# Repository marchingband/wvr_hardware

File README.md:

# wvr_hardware

Find the Kicad files in their respective folders, more will be added with time.  
We have done our best to make these files portable, using project specific libraries.  
These are for Kicad V5.

In the JLC_PCB folder you can find all the files needed to order WVR BASIC from JLC with assembly. Kindly donated by Robin of Atonal Circuits.

There are 3 branches. v2.1 is the newest one, which includes a footprint for the XIAO SAMD21 on the back side, and a resistor on the front side to connect the UARTS.
click "main" above, and select v2.1 to move to this new branch
  
# pinouts

<pre>
pinout for WVR :

WVR PIN | MAKERS BOARD PIN | ESP32 GPIO | NOTES  
  
D0      |       14         |    3       | FTDI RX  
D1      |       13         |    1       | FTDI TX  
D2      |       12         |    21      | USB MIDI In (when using USB backpack firmware)  
D3      |       11         |    19      |  
D4      |       10         |    18      |  
D5      |       9          |    5       |  
D6      |       8          |    0       | no ADC when WIFI active, strapping pin for bootloader mode (must be high or floating at boot)  
D7      |       7          |    36      | no built-in pullups, input only  
D8      |       6          |    39      | no built-in pullups, input only  
D9      |       5          |    34      | no built-in pullups, input only  
D10     |       4          |    35      | no built-in pullups, input only  
D11     |       3          |    32      |  
D12     |       2          |    33      |  
D13     |       1          |    27      | no ADC when WIFI active  
</pre>  
  
# wiring diagram
Example of powering with the 5v pin, instead of the USB jack, with breadboard-compatible push button and headphone jack attached.  
When WVR's WiFi is active, current consumption can peak significantly, as the radio consumes a fair bit of current. We recommend a PSU that provides 500mA or more at 5v. Any voltage between 5vDC and 9vDC will work, but keep in mind that higher voltage will result in more heat produced by the voltage regulator, which can get very hot! If you experience brown-outs during the boot sequence, try a PSU with a higher current rating.  

# wiring diagram for midi control
Example of controlling WVR from a RPi Pico using MIDI. Note that because MIDI is optically isolated, both boards can be powered independantly, by USB, or otherwise. Thus there are no power rails connected in this diagram. It is also OK to power both boards from the same power source, it is just not necissary to do so.  
Note also, the MIDI signal does not use a ground connection. MIDI is a 2-line protocol, just +5v and TX are needed.  
Here is a great Arduino library to generate MIDI signals from the RPi Pico, or most any other microcontroller: https://github.com/FortySevenEffects/arduino_midi_library

This code snippet for the PiPico sends some basic MIDI messages and flashes the onboard LED.
```
#include <Arduino.h>
#include <MIDI.h>

using Transport = MIDI_NAMESPACE::SerialMIDI<HardwareSerial>;
Transport serialMIDI(Serial1);
MIDI_NAMESPACE::MidiInterface<Transport> MIDI((Transport&)serialMIDI);

void setup()
{
  pinMode(LED_BUILTIN, OUTPUT);
  MIDI.begin(MIDI_CHANNEL_OMNI); // Launch MIDI
}

void loop()
{
    MIDI.sendNoteOn(40, 127, 1);    // Send a Note (pitch 40, velocity 127 on channel 1)
    digitalWrite(LED_BUILTIN, HIGH);
    delay(1000);                    // Wait for a second
    MIDI.sendNoteOff(40, 0, 1);     // Stop the note
    digitalWrite(LED_BUILTIN, LOW);
    delay(1000);
}
```

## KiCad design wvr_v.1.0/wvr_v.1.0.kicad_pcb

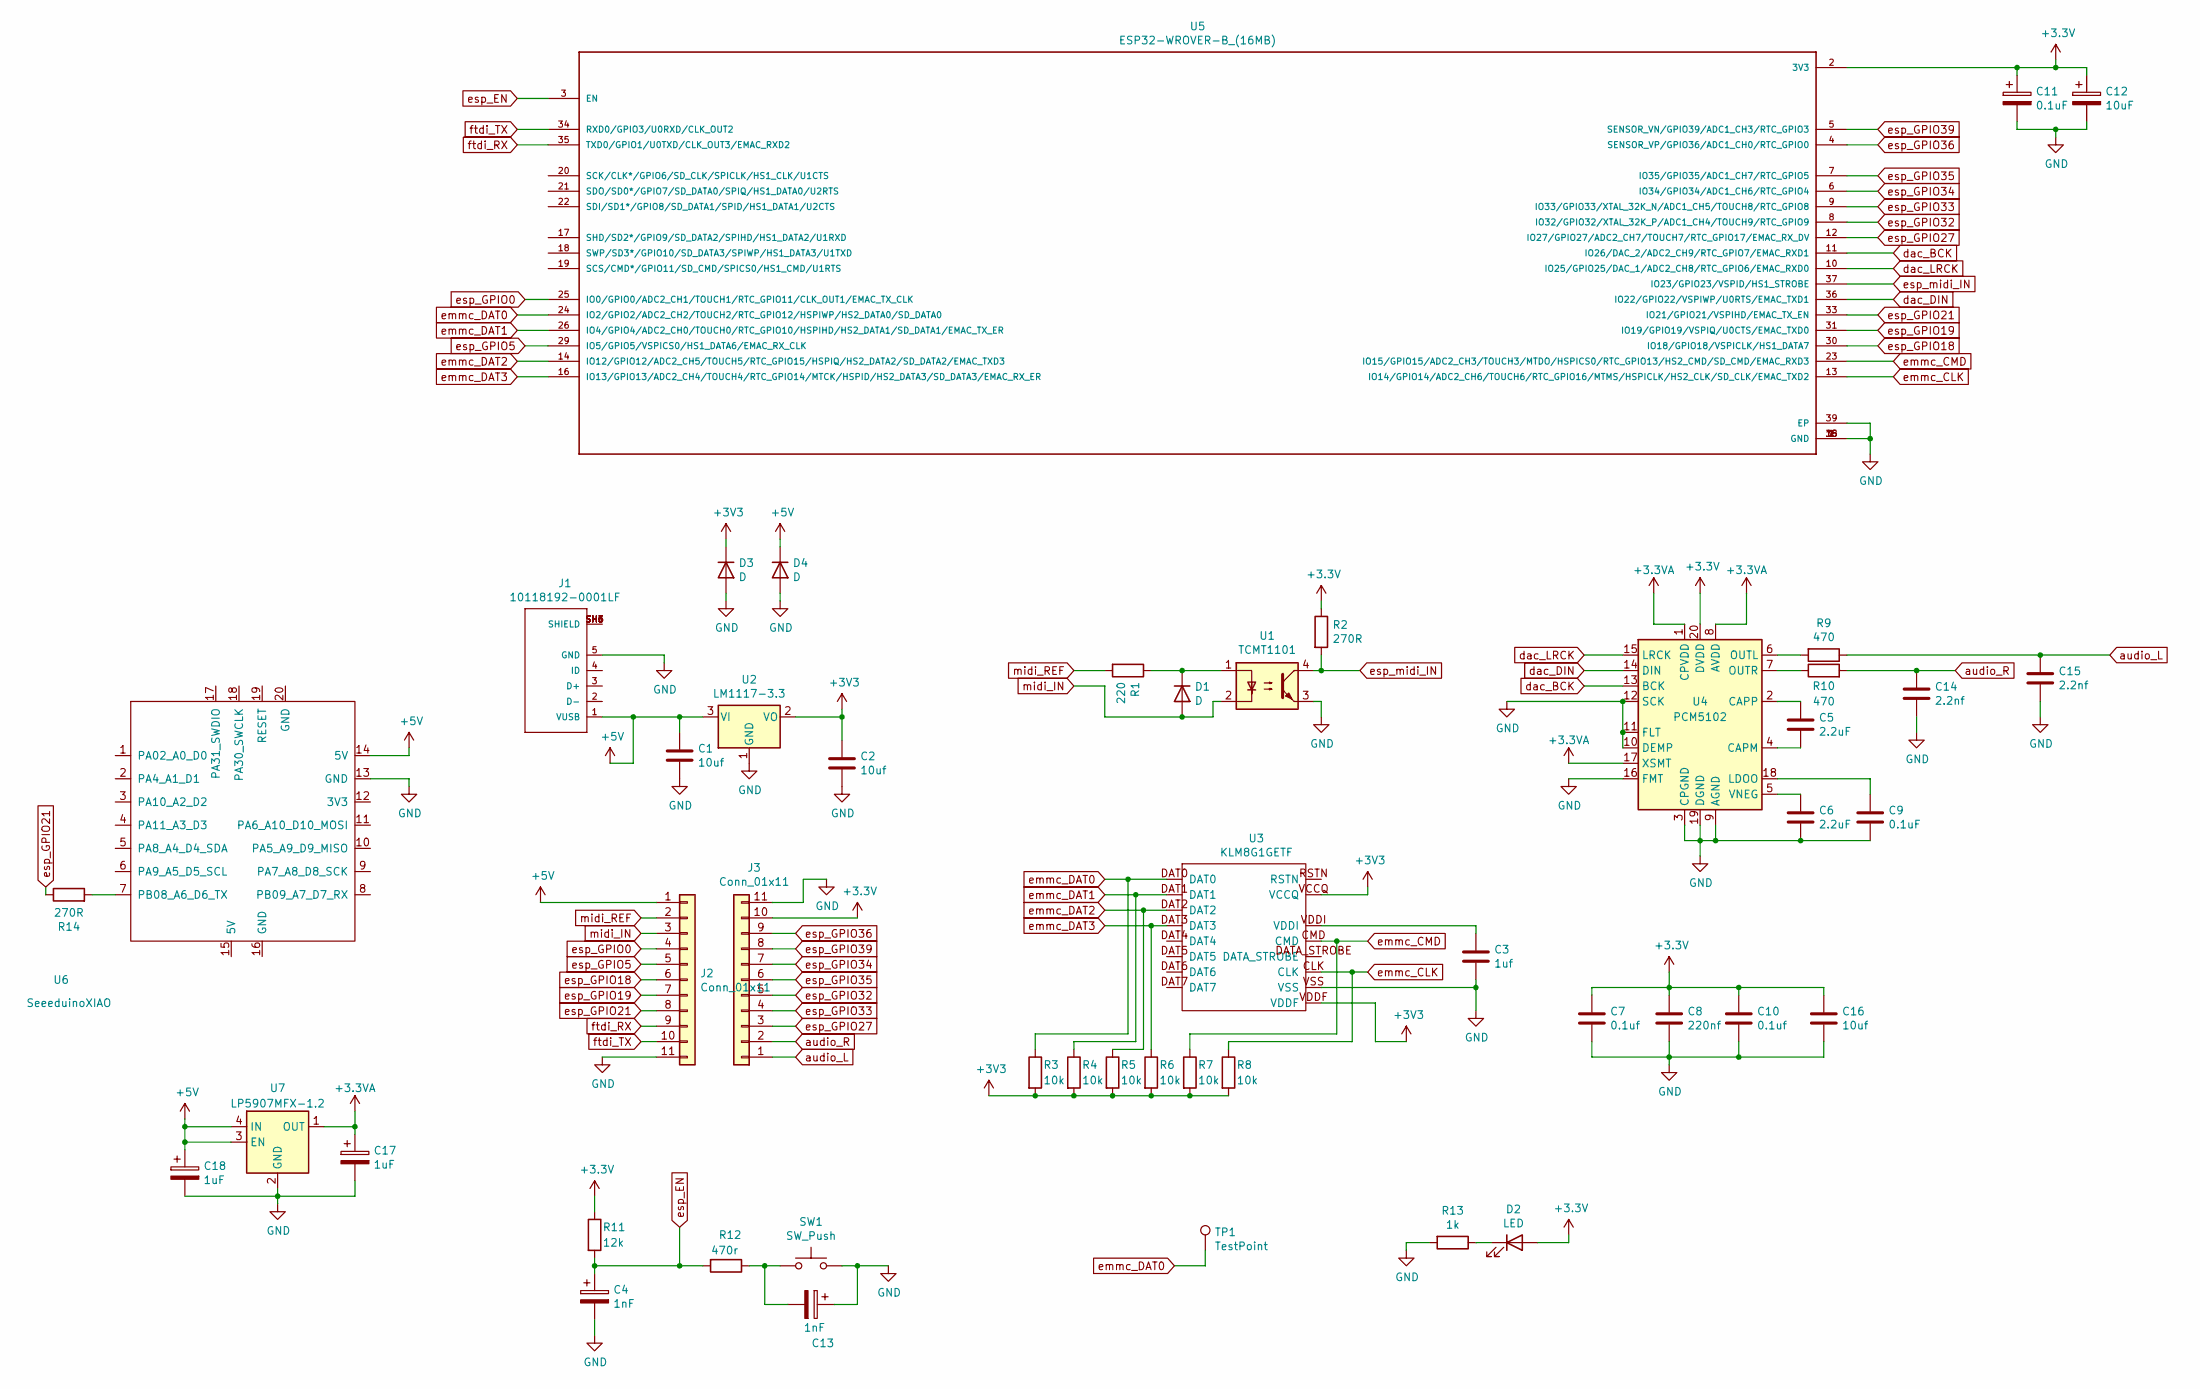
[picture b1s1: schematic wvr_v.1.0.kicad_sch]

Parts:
C1, C2, C16: 10uf; C_0402_1005Metric
C3: 1uf; C_0402_1005Metric
C4, C13: 1nF; C_0402_1005Metric
C5, C6: 2.2uF; C_0402_1005Metric
C7, C10: 0.1uf; C_0402_1005Metric
C8: 220nf; C_0402_1005Metric
C9, C11: 0.1uF; C_0402_1005Metric
C12: 10uF; C_0402_1005Metric
C14, C15: 2.2nf; C_0402_1005Metric
C17, C18: 1uF; C_0402_1005Metric
D1, D3, D4: D; D_SOD-323
D2: LED; LED_0603_1608Metric
J1: 10118192-0001LF; USB-MICRO-B_C40942
J2: Conn_01x11; CAST_HEADER_11_LEFT_2
J3: Conn_01x11; CAST_HEADER_11_RIGHT_2
R1: 220; R_0402_1005Metric
R2, R14: 270R; R_0402_1005Metric
R3, R4, R5, R6, R7, R8: 10k; R_0402_1005Metric
R9, R10: 470; R_0402_1005Metric
R11: 12k; R_0402_1005Metric
R12: 470r; R_0402_1005Metric
R13: 1k; R_0402_1005Metric
SW1: SW_Push; SW_Push_SPST_NO_Alps_SKRK
TP1: TestPoint; TestPoint_Pad_D1.5mm
U1: TCMT1101; SOP-4_4.4x2.6mm_P1.27mm
U2: LM1117-3.3; SOT-223-3_TabPin2; LCSC C23984
U3: KLM8G1GETF; KLM8G1GETF_ALL_PADS; LCSC C499918
U4: PCM5102; TSSOP-20_4.4x6.5mm_P0.65mm; LCSC C131154
U5: ESP32-WROVER-B_(16MB); XCVR_ESP32-WROVER-B_(16MB); LCSC C529591
U6: SeeeduinoXIAO; Seeeduino XIAO-MOUDLE14P-2.54-21X17.8MM
U7: LP5907MFX-1.2; Texas_X2SON-4_1x1mm_P0.65mm

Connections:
+5V: C1.1, C18.1, D4.1 (K), J1.1 (VUSB), J2.1, U2.3 (VI), U6.14 (5V), U7.3 (EN), U7.4 (IN)
GND: C1.2, C2.2, C3.2, C4.2, C6.2, C7.2, C8.2, C9.2, C10.2, C11.2, C12.2, C13.1, C14.2, C15.2, C16.2, C17.2, C18.2, D3.2 (A), D4.2 (A), J1.5 (GND), J2.11, J3.11, R13.2, SW1.2, U1.3, U2.1 (GND), U3.VSS, U4.3 (CPGND), U4.9 (AGND), U4.10 (DEMP), U4.11 (FLT), U4.12 (SCK), U4.16 (FMT), U4.19 (DGND), U5.1 (GND), U5.15 (GND), U5.38 (GND), U5.39 (EP), U6.13 (GND), U7.2 (GND)
unnamed: C3.1, U3.VDDI
unnamed: C5.1, U4.2 (CAPP)
unnamed: C5.2, U4.4 (CAPM)
unnamed: C6.1, U4.5 (VNEG)
unnamed: C9.1, U4.18 (LDOO)
unnamed: C13.2, R12.1, SW1.1
unnamed: D1.1 (K), R1.1, U1.1
unnamed: D2.1 (K), R13.1
unnamed: J1.SH3 (SHIELD), J1.SH4 (SHIELD), J1.SH5 (SHIELD), J1.SH6 (SHIELD)
unnamed: R9.2, U4.6 (OUTL)
unnamed: R10.1, U4.7 (OUTR)
unnamed: R14.2, U6.7 (PB08_A6_D6_TX)
audio_L: C15.1, J3.1, R9.1
audio_R: C14.1, J3.2, R10.2
dac_BCK: U4.13 (BCK), U5.11 (IO26/DAC_2/ADC2_CH9/RTC_GPIO7/EMAC_RXD1)
dac_DIN: U4.14 (DIN), U5.36 (IO22/GPIO22/VSPIWP/U0RTS/EMAC_TXD1)
dac_LRCK: U4.15 (LRCK), U5.10 (IO25/GPIO25/DAC_1/ADC2_CH8/RTC_GPIO6/EM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)
emmc_CLK: R8.1, U3.CLK, U5.13 (IO14/GPIO14/ADC2_CH6/TOUCH6/RTC_GPIO16/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)
emmc_CMD: R7.1, U3.CMD, U5.23 (IO15/GPIO15/ADC2_CH3/TOUCH3/MTDO/HSPICS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)
emmc_DAT0: R3.1, TP1.1, U3.DAT0, U5.24 (IO2/GPIO2/ADC2_CH2/TOUCH2/RTC_GPIO12/HS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); also elsewhere on the board
emmc_DAT1: R4.1, U3.DAT1, U5.26 (IO4/GPIO4/ADC2_CH0/TOUCH0/RTC_GPIO10/HS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)
emmc_DAT2: R5.1, U3.DAT2, U5.14 (IO12/GPIO12/ADC2_CH5/TOUCH5/RTC_GPIO15/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)
emmc_DAT3: R6.1, U3.DAT3, U5.16 (IO13/GPIO13/ADC2_CH4/TOUCH4/RTC_GPIO14/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)
esp_EN: C4.1, R11.2, R12.2, U5.3 (EN)
esp_GPIO0: J2.4, U5.25 (IO0/GPIO0/ADC2_CH1/TOUCH1/RTC_GPIO11/CL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)
esp_GPIO5: J2.5, U5.29 (IO5/GPIO5/VSPICS0/HS1_DATA6/EMAC_RX_CLK)
esp_GPIO18: J2.6, U5.30 (IO18/GPIO18/VSPICLK/HS1_DATA7)
esp_GPIO19: J2.7, U5.31 (IO19/GPIO19/VSPIQ/U0CTS/EMAC_TXD0)
esp_GPIO21: J2.8, R14.1, U5.33 (IO21/GPIO21/VSPIHD/EMAC_TX_EN)
esp_GPIO27: J3.3, U5.12 (IO27/GPIO27/ADC2_CH7/TOUCH7/RTC_GPIO17/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)
esp_GPIO32: J3.5, U5.8 (IO32/GPIO32/XTAL_32K_P/ADC1_CH4/TOUCH9/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)
esp_GPIO33: J3.4, U5.9 (IO33/GPIO33/XTAL_32K_N/ADC1_CH5/TOUCH8/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)
esp_GPIO34: J3.7, U5.6 (IO34/GPIO34/ADC1_CH6/RTC_GPIO4)
esp_GPIO35: J3.6, U5.7 (IO35/GPIO35/ADC1_CH7/RTC_GPIO5)
esp_GPIO36: J3.9, U5.4 (SENSOR_VP/GPIO36/ADC1_CH0/RTC_GPIO0)
esp_GPIO39: J3.8, U5.5 (SENSOR_VN/GPIO39/ADC1_CH3/RTC_GPIO3)
esp_midi_IN: R2.2, U1.4, U5.37 (IO23/GPIO23/VSPID/HS1_STROBE)
ftdi_RX: J2.9, U5.35 (TXD0/GPIO1/U0TXD/CLK_OUT3/EMAC_RXD2)
ftdi_TX: J2.10, U5.34 (RXD0/GPIO3/U0RXD/CLK_OUT2)
midi_IN: D1.2 (A), J2.3, U1.2
midi_REF: J2.2, R1.2

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
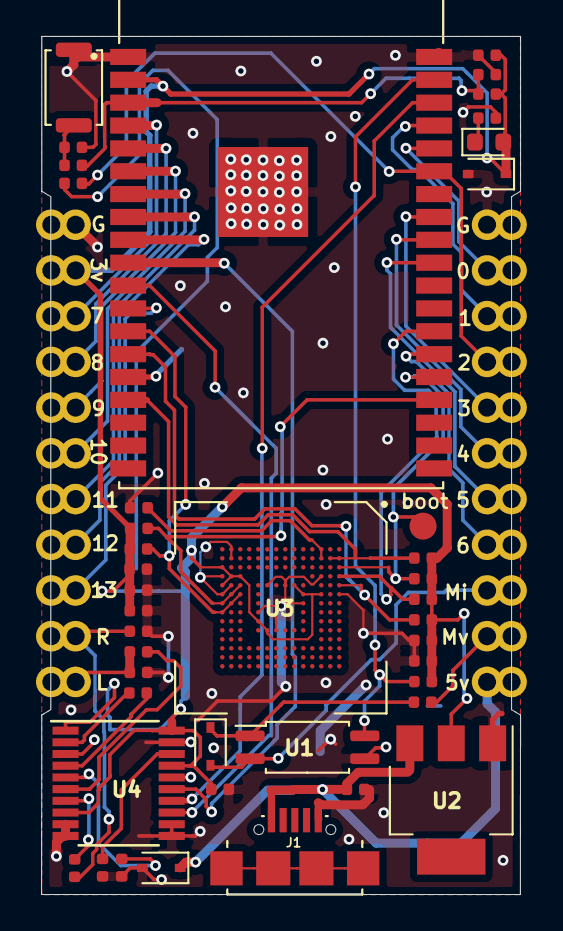
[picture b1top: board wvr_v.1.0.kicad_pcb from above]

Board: 2 copper layers, 26.6 x 47.7 mm, 45 parts (1 on the bottom side), 44 nets.

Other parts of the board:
boot: TestPoint; TestPoint_Pad_D1.5mm

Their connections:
emmc_DAT0: boot.1; also elsewhere on the board

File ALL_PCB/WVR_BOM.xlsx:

Item # | Designator | *Qty | Manufacturer | *Mfg Part # | Description / Value | *Package/Footprint | Type | Your Instructions / Notes
1 | C1,C2,C16 | 3 |  | C15525 | 10uf | 0402 | SMD
2 | C7,C10 | 2 |  | C1525 | 0.1uf | 0402 | SMD
3 | C12 | 1 |  | C15525 | 10uF | 0402 | SMD
4 | C14,C15 | 2 |  | C1531 | 2.2nf | 0402 | SMD
5 | C3 | 1 |  | C52923 | 1uf | 0402 | SMD
6 | C4,C13 | 2 |  | C1523 | 1nF | 0402 | SMD
7 | C5,C6 | 2 |  | C12530 | 2.2uF | 0402 | SMD
9 | C8 | 1 |  | C16772 | 220nf | 402 | SMD
10 | C9,C11 | 2 |  | C1525 | 0.1uF | 402 | SMD
11 | D1,D3,D4 | 3 |  | C2128 | D | SOD-323 | SMD
12 | D2 | 1 |  | C72041 | LED | 603 | SMD
13 | J1 | 1 |  | C40942 | usb b micro | 0402 | SMD
14 | R1 | 1 |  | C25091 | 220 | 0402 | SMD
15 | R11 | 1 |  | C25752 | 12k | 0402 | SMD
16 | R2 | 1 |  | C423200 | 280 | 402 | SDM
17 | R3,R4,R5,R6,R7,R8 | 6 |  | C25744 | 10k | 402 | SMD
18 | R9,R10,R12,R13,R14 | 4 |  | C25117 | 470 | 402 | SMD
19 | SW1 | 1 |  | C720477 | SW_Push | SKRK | SMD
20 | U1 | 1 |  | C32565 | EL3H7 | SOP-4 | SMD
21 | U2 | 1 |  | C6186 | LM1117-3.3 | SOT-223 SOT-223 | SMD
22 | U3 | 1 |  | C499918 | KLM8G1GETF | FBGA-153 | SMD
23 | U4 | 1 |  | C1540069 | PCM5100 | TSSOP-20 | SMD
24 | U5 | 1 |  | C503591 | ESP32-WROVER-B | XCVR_ESP32-WROVER-B | SMD

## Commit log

2021-08-06 readme
2021-08-06 shematic.png
2021-08-06 update schematic resistor values
2022-03-15 add JLC
2022-05-18 add images
2022-07-24 switch
2022-09-26 add usb midi resistor to front
2022-09-26 update silk layer, clean up .cpl file, print gerbers
2022-09-26 remove headers
2022-10-21 add dev board schematic pdf
2023-04-13 add wiring diagram
2023-04-30 update pinout
2023-05-04 add 2nd LDO for 3.3VA and AGND
2023-05-06 v3.0
2023-05-18 add midi wiring diagram
2023-05-28 Create LICENSE
2024-09-01 update IP Address on silk, update jlc component codes
2024-09-05 Add files via upload
    Update midi wiring diagram

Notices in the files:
README.md:
License: GPL v3
